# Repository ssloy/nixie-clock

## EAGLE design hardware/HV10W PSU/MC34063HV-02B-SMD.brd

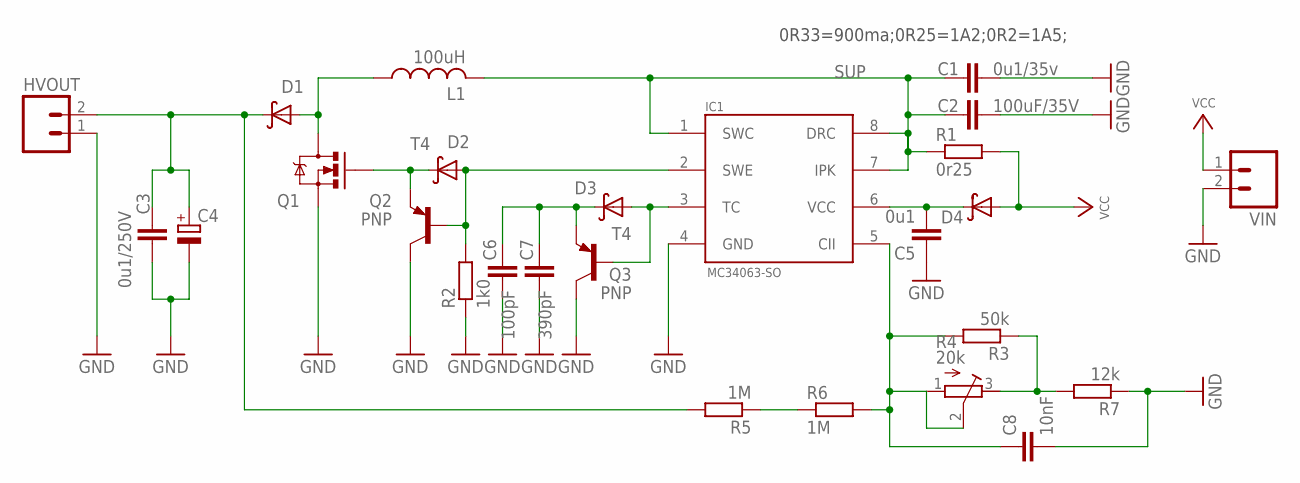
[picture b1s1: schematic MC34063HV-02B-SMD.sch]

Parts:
C1: 0u1/35v; C1206
C2: 100uF/35V; C1206
C3: 0u1/250V; C1206K
C4: CPOL-EUE5-10.5; E5-10,5
C5: 0u1; C0603
C6: 100pF; C0603
C7: 390pF; C0603
C8: 10nF; C0603
D1, D4: DIODE-SCHOTTKYSMA; SMA-DIODE
D2: T4; SOD123
D3: T4; SOD323-W
HVOUT: M02PTH; 1X02
IC1: MC34063-SO; SO8
L1: 100uH; INDUCTOR11X11
Q1: MOSFET-NCHANNELTO220V-BH2; TO220V-BIGHOLE-V2
Q2, Q3: PNP; SOT23-BEC
R1: 0r25; R1206
R2: 1k0; R0603
R3: 50k; R0603
R4: 20k; RTRIM3296W
R5, R6: 1M; R1206
R7: 12k; R0603
VIN: M02PTH; 1X02

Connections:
GND: C1.2, C2.2, C3.2, C4.-, C5.1, C6.1, C7.1, C8.2, HVOUT.1, IC1.4 (GND), Q1.3 (S), Q2.3 (C), Q3.3 (C), R2.1, R7.1, VIN.2
HVFB: C8.1, IC1.5 (CII), R3.2, R4.1 (A), R4.2 (S), R6.2
unnamed: C6.2, C7.2, D3.C, Q3.2 (E)
unnamed: D2.A, IC1.2 (SWE), Q2.1 (B), R2.2
unnamed: D2.C, Q1.1 (G), Q2.2 (E)
unnamed: C5.2, D4.C, IC1.6 (VCC)
unnamed: C3.1, C4.+, D1.C, HVOUT.2, R5.2
unnamed: D3.A, IC1.3 (TC), Q3.1 (B)
unnamed: R5.1, R6.1
unnamed: R3.1, R4.3 (E), R7.2
SUP: C1.1, C2.1, IC1.1 (SWC), IC1.7 (IPK), IC1.8 (DRC), L1.P$2 (2), R1.1
SW: D1.A, L1.P$1 (1), Q1.2 (D)
VCC: D4.A, R1.2, VIN.1

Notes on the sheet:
0R33=900ma;0R25=1A2;0R2=1A5;

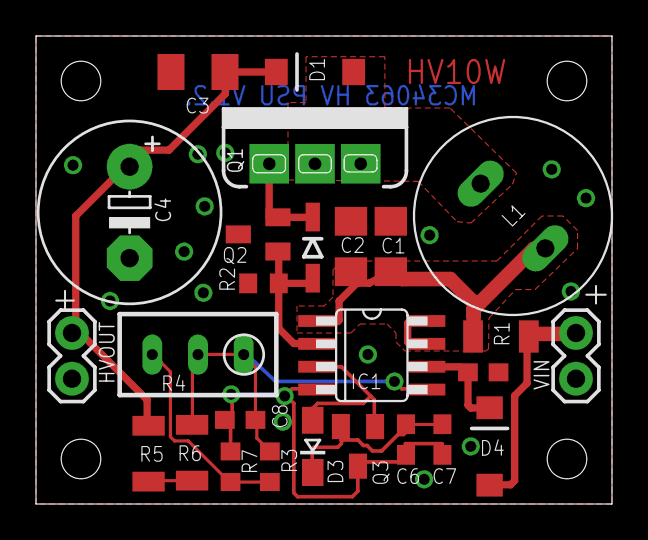
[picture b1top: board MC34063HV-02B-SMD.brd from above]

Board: 2 copper layers, 32.0 x 26.0 mm, 27 parts (1 on the bottom side), 13 nets.

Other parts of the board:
U$1: HV03

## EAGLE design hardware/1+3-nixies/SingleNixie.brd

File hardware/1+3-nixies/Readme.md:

# beware of bugs

Some tracks are missing in the PCB layout (the schematics are fine).

The single nixie module lacks two tracks:

The triple nixie module lacks one track:

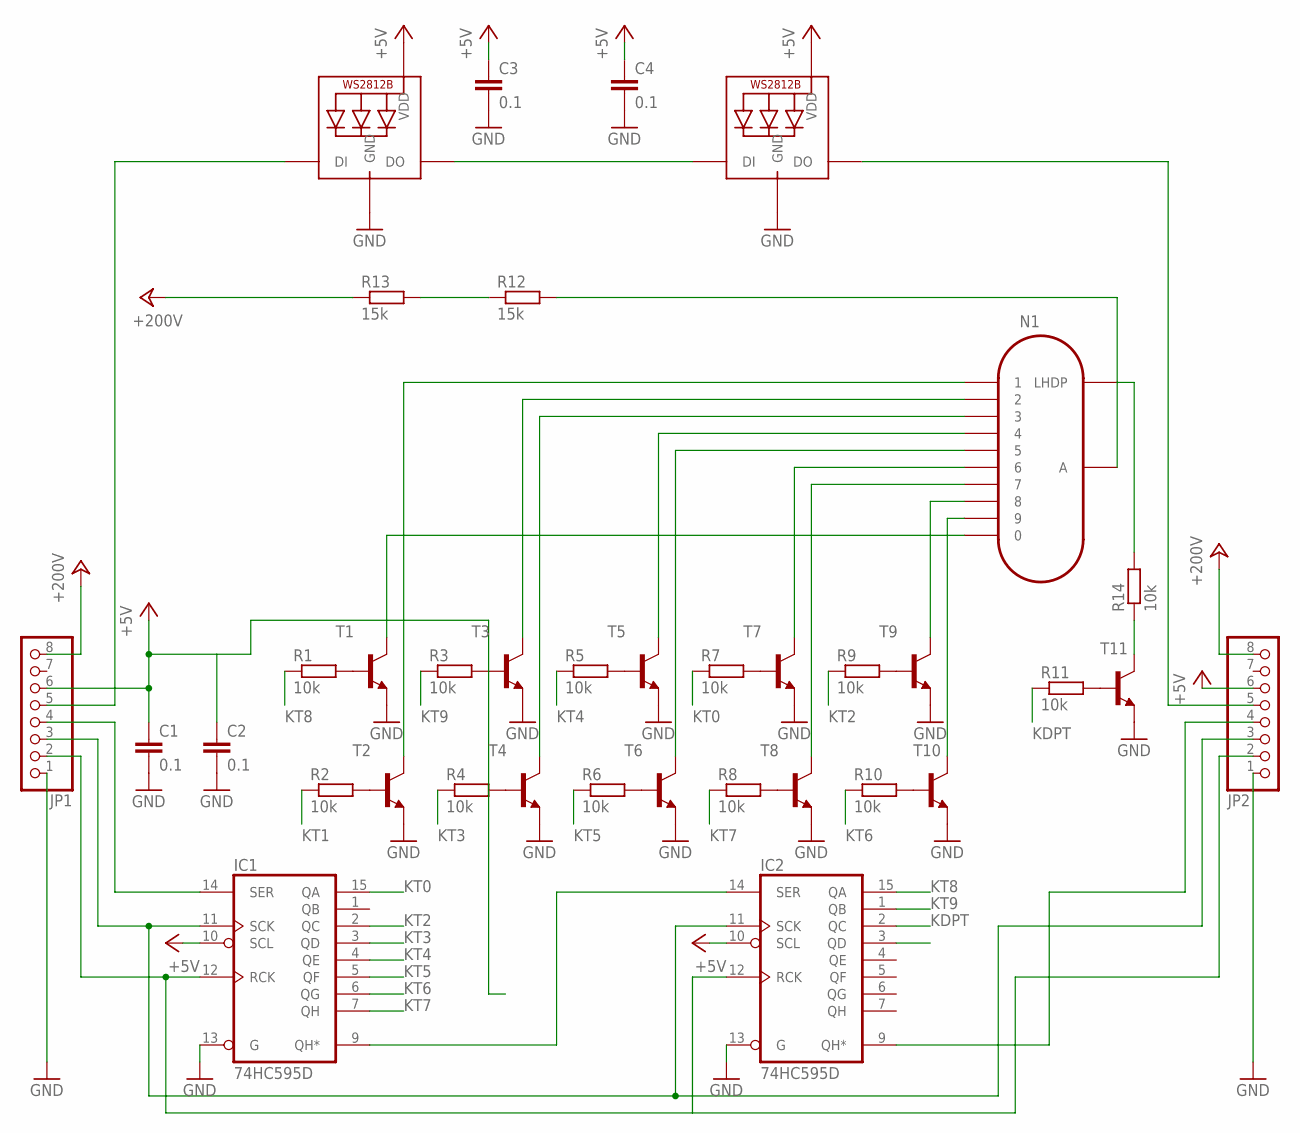
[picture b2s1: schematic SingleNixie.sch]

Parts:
C1, C2, C3, C4: 0.1; C0805
IC1, IC2: 74HC595D; SO16
JP1, JP2: HEADER-1X8ROUND; 1X08_ROUND
LED1, LED2: WS2812B3535; LED3535
N1: IN-12B1.5MM; IN-12-1.5
R1, R2, R3, R4, R5, R6, R7, R8, R9, R10, R11, R14: 10k; R0805
R12, R13: 15k; R0805
T1, T2, T3, T4, T5, T6, T7, T8, T9, T10, T11: MMBTA42LT1-NPN-SOT23-BEC; SOT23-BEC

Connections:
+5V: C1.1, C2.1, C3.1, C4.1, IC1.10 (SCL), IC1.16 (VCC), IC2.10 (SCL), IC2.16 (VCC), JP1.6, JP2.6, LED1.2 (VDD), LED2.2 (VDD)
+200V: JP1.8, JP2.8, R13.1
ANODE: N1.A, R12.2
GND: C1.2, C2.2, C3.2, C4.2, IC1.8 (GND), IC1.13 (G), IC2.8 (GND), IC2.13 (G), JP1.1, JP2.1, LED1.4 (GND), LED2.4 (GND), T1.E, T2.E, T3.E, T4.E, T5.E, T6.E, T7.E, T8.E, T9.E, T10.E, T11.E
K0: N1.0, T1.C
K1: N1.1, T2.C
K2: N1.2, T3.C
K3: N1.3, T4.C
K4: N1.4, T5.C
K5: N1.5, T6.C
K6: N1.6, T7.C
K7: N1.7, T8.C
K8: N1.8, T9.C
K9: N1.9, T10.C
KDP: N1.LHDP, R14.2
KDPT: IC2.2 (QC), R11.1
KT0: IC1.15 (QA), R7.1
KT1: IC2.3 (QD), R2.1
KT2: IC1.2 (QC), R9.1
KT3: IC1.3 (QD), R4.1
KT4: IC1.4 (QE), R5.1
KT5: IC1.5 (QF), R6.1
KT6: IC1.6 (QG), R10.1
KT7: IC1.7 (QH), R8.1
KT8: IC2.15 (QA), R1.1
KT9: IC2.1 (QB), R3.1
unnamed: R3.2, T3.B
unnamed: R1.2, T1.B
unnamed: R2.2, T2.B
unnamed: R4.2, T4.B
unnamed: R5.2, T5.B
unnamed: R6.2, T6.B
unnamed: R7.2, T7.B
unnamed: R8.2, T8.B
unnamed: R9.2, T9.B
unnamed: R10.2, T10.B
unnamed: LED1.3 (DO), LED2.1 (DI)
unnamed: JP1.5, LED1.1 (DI)
unnamed: JP2.5, LED2.3 (DO)
unnamed: R11.2, T11.B
unnamed: IC1.14 (SER), JP1.4
unnamed: R14.1, T11.C
unnamed: R12.1, R13.2
unnamed: IC1.9 (QH*), IC2.14 (SER)
unnamed: IC1.11 (SCK), IC2.11 (SCK), JP1.3, JP2.3
unnamed: IC1.12 (RCK), IC2.12 (RCK), JP1.2, JP2.2
unnamed: IC2.9 (QH*), JP2.4

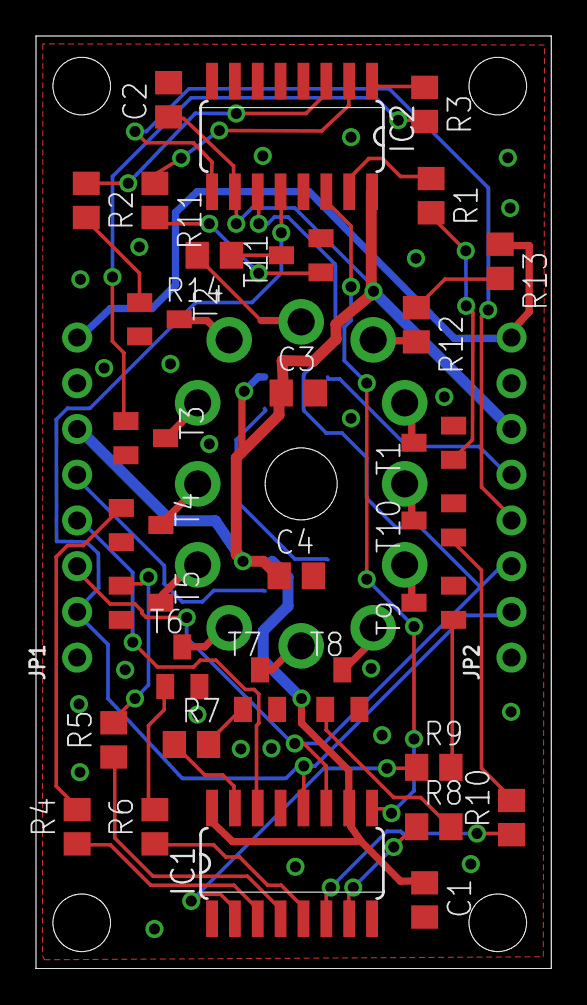
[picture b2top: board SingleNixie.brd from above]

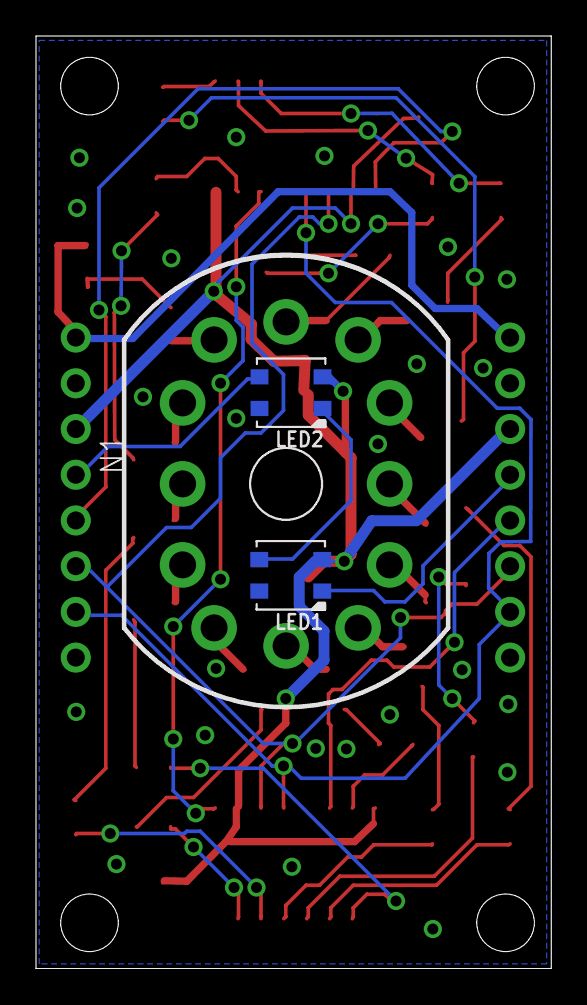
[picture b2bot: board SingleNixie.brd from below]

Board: 2 copper layers, 28.6 x 51.8 mm, 36 parts (3 on the bottom side), 47 nets.

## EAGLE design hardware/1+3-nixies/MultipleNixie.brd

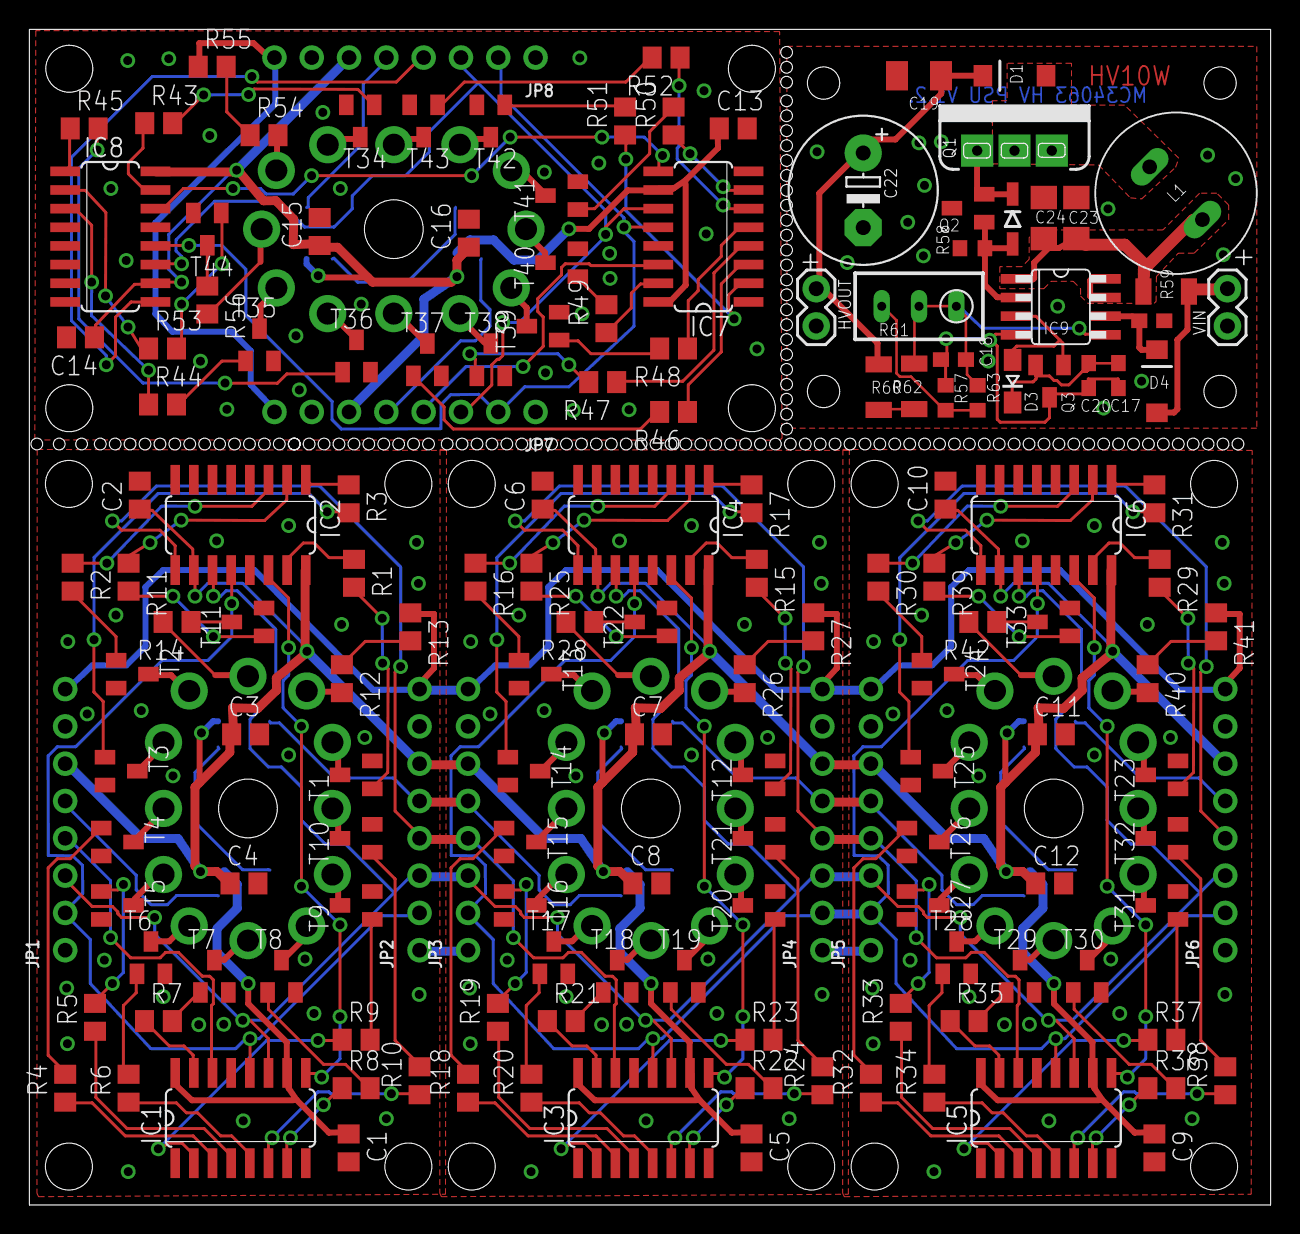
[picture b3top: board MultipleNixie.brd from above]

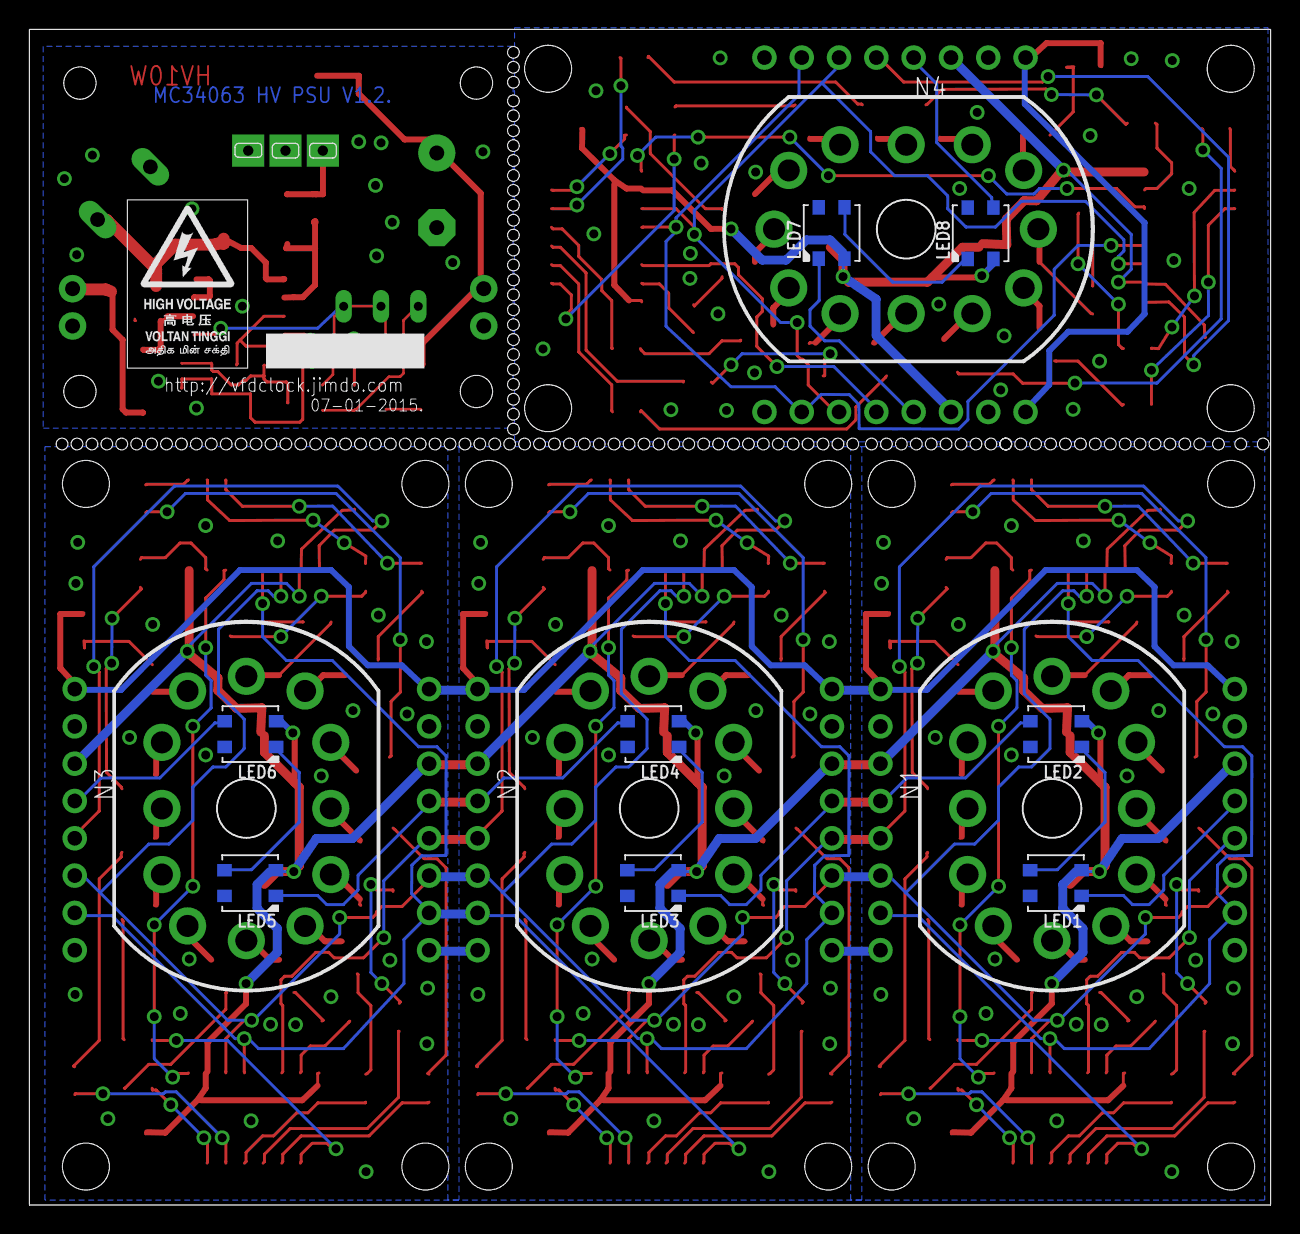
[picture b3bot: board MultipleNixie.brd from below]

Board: 2 copper layers, 84.5 x 80.1 mm, 171 parts (13 on the bottom side), 199 nets.

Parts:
C1, C2, C3, C4, C5, C6, C7, C8, C9, C10, C11, C12, C13, C14, C15, C16: 0.1; C0805
C17: 390pF; C0603
C18: 10nF; C0603
C19: 0u1/250V; C1206K
C20: 100pF; C0603
C21: 0u1; C0603
C22: E5-10,5
C23: 0u1/35v; C1206
C24: 100uF/35V; C1206
D1: DIODE-SCHOTTKYSMA; SMA-DIODE
D2: T4; SOD123
D3: T4; SOD323-W
D4: SMA-DIODE
HVOUT: 1X02
IC1, IC2, IC3, IC4, IC5, IC6, IC7, IC8: 74HC595D; SO16
IC9: MC34063-SO; SO8
JP1, JP2, JP3, JP4, JP5, JP6, JP7, JP8: 1X08_ROUND
L1: 100uH; INDUCTOR11X11
LED1, LED2, LED3, LED4, LED5, LED6, LED7, LED8: WS2812B3535; LED3535
N1, N2, N3, N4: IN-12B1.5MM; IN-12-1.5
Q1: TO220V-BIGHOLE-V2
Q2, Q3: PNP; SOT23-BEC
R1, R2, R3, R4, R5, R6, R7, R8, R9, R10, R11, R14, R15, R16, R17, R18, R19, R20, R21, R22, R23, R24, R25, R28, R29, R30, R31, R32, R33, R34, R35, R36, R37, R38, R39, R42, R43, R44, R45, R46, R47, R48, R49, R50, R51, R52, R53, R56: 10k; R0805
R12, R13, R26, R27, R40, R41, R54, R55: 15k; R0805
R57: 12k; R0603
R58: 1k0; R0603
R59: 0r25; R1206
R60, R62: 1M; R1206
R61: 20k; RTRIM3296W
R63: 50k; R0603
T1, T2, T3, T4, T5, T6, T7, T8, T9, T10, T11, T12, T13, T14, T15, T16, T17, T18, T19, T20, T21, T22, T23, T24, T25, T26, T27, T28, T29, T30, T31, T32, T33, T34, T35, T36, T37, T38, T39, T40, T41, T42, T43, T44: SOT23-BEC
U$1: HV03
VIN: 1X02

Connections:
+5V: C1.1, C2.1, C3.1, C4.1, IC1.10, IC1.16, IC2.10, IC2.16, JP1.6, JP2.6, LED1.2, LED2.2
+5V1: C5.1, C6.1, C7.1, C8.1, IC3.10, IC3.16, IC4.10, IC4.16, JP3.6, JP4.6, LED3.2, LED4.2
+5V2: C9.1, C10.1, C11.1, C12.1, IC5.10, IC5.16, IC6.10, IC6.16, JP5.6, JP6.6, LED5.2, LED6.2
+5V3: C13.1, C14.1, C15.1, C16.1, IC7.10, IC7.16, IC8.10, IC8.16, JP7.6, JP8.6, LED7.2, LED8.2
+200V: JP1.8, JP2.8, R13.1
+200V1: JP3.8, JP4.8, R27.1
+200V2: JP5.8, JP6.8, R41.1
+200V3: JP7.8, JP8.8, R55.1
ANODE: N1.A, R12.2
ANODE1: N2.A, R26.2
ANODE2: N3.A, R40.2
ANODE3: N4.A, R54.2
GND: C1.2, C2.2, C3.2, C4.2, C5.2, C6.2, C7.2, C8.2, C9.2, C10.2, C11.2, C12.2, IC1.8, IC1.13, IC2.8, IC2.13, IC3.8, IC3.13, IC4.8, IC4.13, IC5.8, IC5.13, IC6.8, IC6.13, JP1.1, JP2.1, JP3.1, JP4.1, JP5.1, JP6.1, LED1.4, LED2.4, LED3.4, LED4.4, LED5.4, LED6.4, T1.E, T2.E, T3.E, T4.E, T5.E, T6.E, T7.E, T8.E, T9.E, T10.E, T11.E, T12.E, T13.E, T14.E, T15.E, T16.E, T17.E, T18.E, T19.E, T20.E, T21.E, T22.E, T23.E, T24.E, T25.E, T26.E, T27.E, T28.E, T29.E, T30.E, T31.E, T32.E, T33.E
GND3: C13.2, C14.2, C15.2, C16.2, IC7.8, IC7.13, IC8.8, IC8.13, JP7.1, JP8.1, LED7.4, LED8.4, T34.E, T35.E, T36.E, T37.E, T38.E, T39.E, T40.E, T41.E, T42.E, T43.E, T44.E
GND4: C17.1, C18.2, C19.2, C20.1, C21.1, C22.-, C23.2, C24.2, HVOUT.1, IC9.4, Q1.3, Q2.3, Q3.3, R57.1, R58.1, VIN.2
HVFB: C18.1, IC9.5, R61.1, R61.2, R62.2, R63.2
K0: N1.0, T1.C
K1: N1.1, T2.C
K2: N1.2, T3.C
K3: N1.3, T4.C
K4: N1.4, T5.C
K5: N1.5, T6.C
K6: N1.6, T7.C
K7: N1.7, T8.C
K8: N1.8, T9.C
K9: N1.9, T10.C
K10: N2.0, T12.C
K11: N2.1, T13.C
K12: N2.2, T14.C
K13: N2.3, T15.C
K14: N2.4, T16.C
K15: N2.5, T17.C
K16: N2.6, T18.C
K17: N2.7, T19.C
K18: N2.8, T20.C
K19: N2.9, T21.C
K20: N3.0, T23.C
K21: N3.1, T24.C
K22: N3.2, T25.C
K23: N3.3, T26.C
K24: N3.4, T27.C
K25: N3.5, T28.C
K26: N3.6, T29.C
K27: N3.7, T30.C
K28: N3.8, T31.C
K29: N3.9, T32.C
K30: N4.0, T34.C
K31: N4.1, T35.C
K32: N4.2, T36.C
K33: N4.3, T37.C
K34: N4.4, T38.C
K35: N4.5, T39.C
K36: N4.6, T40.C
K37: N4.7, T41.C
K38: N4.8, T42.C
K39: N4.9, T43.C
KDP: N1.LHDP, R14.2
KDP1: N2.LHDP, R28.2
KDP2: N3.LHDP, R42.2
KDP3: N4.LHDP, R56.2
KDPT: IC2.2, R11.1
KDPT1: IC4.2, R25.1
KDPT2: IC6.2, R39.1
KDPT3: IC8.2, R53.1
KT0: IC1.15, R7.1
KT1: IC2.3, R2.1
KT2: IC1.2, R9.1
KT3: IC1.3, R4.1
KT4: IC1.4, R5.1
KT5: IC1.5, R6.1
KT6: IC1.6, R10.1
KT7: IC1.7, R8.1
KT8: IC2.15, R1.1
KT9: IC2.1, R3.1
KT10: IC3.15, R21.1
KT11: IC4.3, R16.1
KT12: IC3.2, R23.1
KT13: IC3.3, R18.1
KT14: IC3.4, R19.1
KT15: IC3.5, R20.1
KT16: IC3.6, R24.1
KT17: IC3.7, R22.1
KT18: IC4.15, R15.1
KT19: IC4.1, R17.1
KT20: IC5.15, R35.1
KT21: IC6.3, R30.1
KT22: IC5.2, R37.1
KT23: IC5.3, R32.1
KT24: IC5.4, R33.1
KT25: IC5.5, R34.1
KT26: IC5.6, R38.1
KT27: IC5.7, R36.1
KT28: IC6.15, R29.1
KT29: IC6.1, R31.1
KT30: IC7.15, R49.1
KT31: IC8.3, R44.1
KT32: IC7.2, R51.1
KT33: IC7.3, R46.1
KT34: IC7.4, R47.1
KT35: IC7.5, R48.1
KT36: IC7.6, R52.1
KT37: IC7.7, R50.1
KT38: IC8.15, R43.1
KT39: IC8.1, R45.1
unnamed: R3.2, T3.B
unnamed: R1.2, T1.B
unnamed: R2.2, T2.B
unnamed: R4.2, T4.B
unnamed: R5.2, T5.B
unnamed: R6.2, T6.B
unnamed: R7.2, T7.B
unnamed: R8.2, T8.B
unnamed: R9.2, T9.B
unnamed: R10.2, T10.B
unnamed: LED1.3, LED2.1
unnamed: JP1.5, LED1.1
unnamed: JP2.5, LED2.3
unnamed: R15.2, T12.B
unnamed: R16.2, T13.B
unnamed: R17.2, T14.B
unnamed: R18.2, T15.B
unnamed: R19.2, T16.B
unnamed: R20.2, T17.B
unnamed: R21.2, T18.B
unnamed: R11.2, T11.B
unnamed: IC1.14, JP1.4
unnamed: R14.1, T11.C
unnamed: R12.1, R13.2
unnamed: IC1.9, IC2.14
unnamed: IC1.11, IC2.11, JP1.3, JP2.3
unnamed: IC1.12, IC2.12, JP1.2, JP2.2
unnamed: IC2.9, JP2.4
unnamed: R22.2, T19.B
unnamed: R23.2, T20.B
unnamed: R24.2, T21.B
unnamed: R25.2, T22.B
unnamed: R28.1, T22.C
unnamed: R26.1, R27.2
unnamed: IC3.14, JP3.4
unnamed: IC3.9, IC4.14
unnamed: IC3.11, IC4.11, JP3.3, JP4.3
unnamed: IC3.12, IC4.12, JP3.2, JP4.2
unnamed: IC4.9, JP4.4
unnamed: LED3.3, LED4.1
unnamed: JP3.5, LED3.1
unnamed: JP4.5, LED4.3
unnamed: R29.2, T23.B
unnamed: R30.2, T24.B
unnamed: R31.2, T25.B
unnamed: R32.2, T26.B
unnamed: R33.2, T27.B
unnamed: R34.2, T28.B
unnamed: R35.2, T29.B
unnamed: R36.2, T30.B
unnamed: R37.2, T31.B
unnamed: R38.2, T32.B
unnamed: R39.2, T33.B
unnamed: R42.1, T33.C
unnamed: R40.1, R41.2
unnamed: IC5.14, JP5.4
unnamed: IC5.9, IC6.14
unnamed: IC5.11, IC6.11, JP5.3, JP6.3
unnamed: IC5.12, IC6.12, JP5.2, JP6.2
unnamed: IC6.9, JP6.4
unnamed: LED5.3, LED6.1
unnamed: JP5.5, LED5.1
unnamed: JP6.5, LED6.3
unnamed: R43.2, T34.B
unnamed: R44.2, T35.B
unnamed: R45.2, T36.B
unnamed: R46.2, T37.B
unnamed: R47.2, T38.B
unnamed: R48.2, T39.B
unnamed: R49.2, T40.B
unnamed: R50.2, T41.B
unnamed: R51.2, T42.B
unnamed: R52.2, T43.B
unnamed: R53.2, T44.B
unnamed: R56.1, T44.C
unnamed: R54.1, R55.2
unnamed: IC7.14, JP7.4
unnamed: IC7.9, IC8.14
unnamed: IC7.11, IC8.11, JP7.3, JP8.3
unnamed: IC7.12, IC8.12, JP7.2, JP8.2
unnamed: IC8.9, JP8.4
unnamed: LED7.3, LED8.1
unnamed: JP7.5, LED7.1
unnamed: JP8.5, LED8.3
unnamed: C17.2, C20.2, D3.C, Q3.2
unnamed: D2.A, IC9.2, Q2.1, R58.2
unnamed: D2.C, Q1.1, Q2.2
unnamed: C19.1, C22.+, D1.C, HVOUT.2, R60.2
unnamed: R60.1, R62.1
unnamed: R57.2, R61.3, R63.1
unnamed: C21.2, D4.C, IC9.6
unnamed: D3.A, IC9.3, Q3.1
SUP: C23.1, C24.1, IC9.1, IC9.7, IC9.8, L1.P$2, R59.1
SW: D1.A, L1.P$1, Q1.2
VCC: D4.A, R59.2, VIN.1

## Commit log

2020-02-22 nixie import
2020-02-29 ИН-12, ИН-15, ИНС-1 data sheets
2020-02-29 EAGLE + gerber files
2020-02-29 bugfix photos
